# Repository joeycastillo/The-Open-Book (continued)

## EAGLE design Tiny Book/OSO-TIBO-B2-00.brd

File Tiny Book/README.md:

# The Tiny Book

Okay I'm going to be completely honest: I have wandered pretty far from the original prompt with this one. The theory was let's make a less expensive, smaller version of the Open Book with as much of its functionality as possible. With variant B, tiny book has instead become a this very quixotic experiment in form and intent, as well as a playground for new tech like [Good Display's touch screen 2.7" EPD](https://zh-tw.buyepaper.com/products/e-ink-touchscreen-27inch-spi-interface-china-e-ink-manufacturer). 

Variant A (with the cap touch slider) is still here but the touch screen kind of renders it moot. Variant B might be a dead end too, but I think it'll have been worth building for the lessons learned along the way. You could also probably redesign it around an ESP32 or NRF52840 and wind up with something more useful, but there are enough new things in this that I figured I'd stick with the SAMD51 for now since I know the chip so well.

- Features that are basically the same as the Open Book:
    - Battery charging
    - Indicator LEDs
    - 4MB QSPI Flash (up from 2MB)
    - MicroSD slot
    - Enable switch
    - Lock button
    - Reset button
    - Serial port
    - VBAT and VBUS monitors
    - Neopixel

- Features that are similar, and the differences:
    - E-Paper screen. Still has partial refresh, but it's smaller (2.7" instead of 4.2").
    - Instead of seven buttons on the front, the E-Paper display has a capacitive touch matrix that detects touches and gestures (and has an interrupt pin).
    - Microcontroller: it's still a SAMD51 with native USB and the same amount of Flash and RAM, but in a QFN48 package, so fewer pins (and sadly less hand-solderability).
    - The I2C port is now JST-SH (STEMMA-QT) due to size constraints.

- Things that are gone, and strategies for doing without:
    - One STEMMA port instead of two, but it's a really versatile pin. It's a DAC pin so you can speaker with it, or configure it as analog input for a mic or potentiometer, PWM it for an LED, run a Neopixel strip or use it as GPIO for a button.
    - Babel chip. The CircuitPython Babel library supports just putting babel.bin on the QSPI flash chip (and since it's twice the size, you'll still have the same amount of space left over for code).
    - Feather compatibility. Sorry. It would be rad to be able to support FeatherWings but there's just not enough room (or pins).

In the course of this experiment, I ran across a very old design concept that imagined a hinged device with a second e-paper screen on a separate board. So I threw one together, using a [9-pin connector](https://www.adafruit.com/product/4350) (like Adafruit uses on the [MONSTER M4SK](https://www.adafruit.com/product/4343)) to bring over SPI, I2C and one extra signal. A SAMD09 on the secondary board (running Adafruit's Seesaw firmware) gives us more pins for more toys.

- Features that got moved to the secondary board or nerfed.
    - Headphone jack (mono instead of stereo) now lives on the secondary board. I sense that the audio quality may not be as good, since the signal has to travel over a 9-pin connector right next to the I2C signals, but we'll find out.
    - Inline mic input moves over with the headphone jack, but alas there is no longer any provision for recording sound (I removed the mic preamp since there's no spare wire to send a mic signal back to the main board). You can still bias the mic input pin and detect up to three types of button presses from the inline button.

- New features on the secondary board
    - A second 2.7" e-paper display. Pads are there for a touch screen and it's in theory connected to pins on the SAMD09 that *could* support I2C. But this would require some kind of passthrough of I2C messages that I'd have to implement in the SAMD09 firmware. My plan is to use a cheaper non-touchscreen display and only have the main screen be a touch screen.
    - An extra status LED. I'm thinking blue?
    - Speaking of LED's: a PWM-enabled bank of five white LED's along the right (left?) side of the board. I call it a reading light, but they'll shine right at your face if you turn them on. There might be some way to fold the device that coaxes them into illuminating the main screen.
    - Speaking of folding the device: a voltage divider labeled "Hinge?" that I might be able to turn into some kind of hinge position detector using a flex PCB. I honestly have no idea.
    - A real-time clock, because I had room (and because I think this could actually make for a sweet clock).
    - A buzzer for making noises (because it might as well be a sweet alarm clock).
    - A light sensor (because I had a pin leftover).

oh also because i haven't written down the board nomenclature anywhere, this is what i mean by OSO-TIBO-B1-00:

- OSO = Oddly Specific Objects
- TIBO = TIny BOok, the project name
- B = Variant, A-Z, some major version of the board with a specific piece of tech or form factor that makes it unique.
- 1 = Subassembly, 1-9. I doubt I'll ever come up with a project that involves more than 9 PCBs.
- 00 = revision, 00-99. Usually starts at 01, but if I'm really unsure of something I'll start at 00.

I'll update this once the boards come in and I actually assemble one of these.

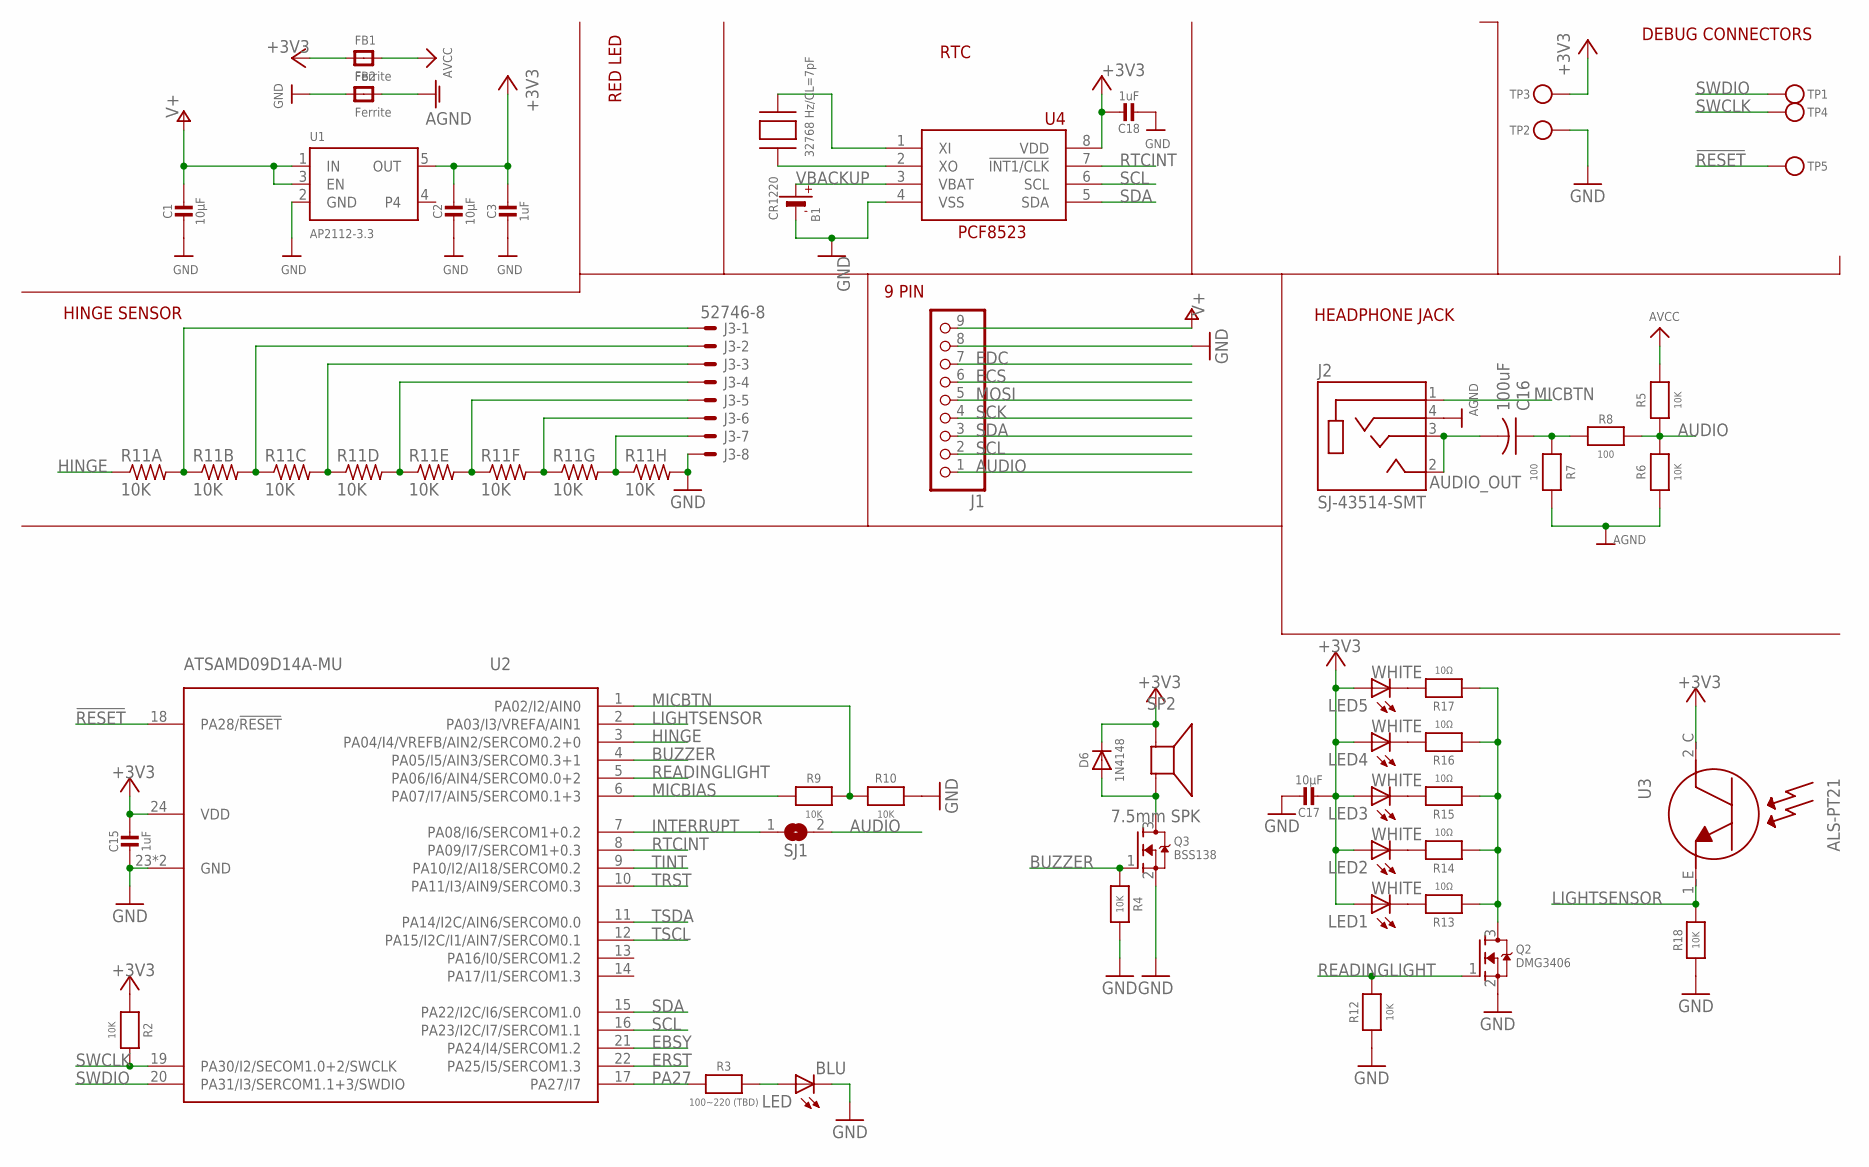
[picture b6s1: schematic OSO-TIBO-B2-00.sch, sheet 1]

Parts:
B1: CR1220
C1, C2, C17: 10µF; 0805-NO
C3, C15, C18: 1uF; 0805-NO
C16: 100uF; C1210
D6: 1N4148; SOD-123
FB1, FB2: Ferrite; 0805
J1: HEADER-1X9_JSTSH; JST_SH9
J2: SJ-43514-SMT; CUI_SJ-43514-SMT
J3: 52746-8
LED: BLU; CHIPLED_0805
LED1, LED2, LED3, LED4, LED5: WHITE; CHIPLED_0805
Q2: DMG3406; SOT23-WIDE
Q3: BSS138; SOT23-WIDE
R2, R4, R9, R10, R12, R18: 10K; 0805-NO
R3: 100~220 (TBD); 0805-NO
R5, R6: 10K; _0805MP
R7, R8: 100; _0805MP
R11: 10K; EXB2HV
R13, R14, R15, R16, R17: 10Ω; 0805-NO
SJ1: SOLDERJUMPERREFLOW_NOPASTE; SOLDERJUMPER_REFLOW_NOPASTE
SP2: 7.5mm SPK; BUZZER_SMT_5MM
TP1, TP2, TP3, TP4, TP5: TESTPOINTROUND2MMNO; TESTPOINT_ROUND_2MM_NO
U1: AP2112-3.3; SOT23-5
U2: ATSAMD09D14A-MU; QFN24_4MM
U3: ALS-PT21; ALS-PT26-21C
U4: PCF8523T; SOIC8_150MIL
X1: 32768 Hz/CL=7pF; XTAL3215

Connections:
!RESET: TP5.P$1, U2.18 (PA28/!RESET)
+3V3: C2.1, C3.1, C15.1, C17.2, C18.1, D6.C, FB1.1, LED1.A, LED2.A, LED3.A, LED4.A, LED5.A, R2.1, SP2.-, TP3.P$1, U1.5 (OUT), U2.24 (VDD), U3.2_C (C), U4.8 (VDD); also elsewhere on the board
AGND: FB2.2, J2.4 (RING2), R6.2, R7.1
AUDIO: J1.1, R5.2, R6.1, R8.1, SJ1.2
AUDIO_OUT: C16.2, J2.2 (TIP), J2.3 (RING1)
AVCC: FB1.2, R5.1
BUZZER: Q3.1 (G), R4.1, U2.4 (PA05/I5/AIN3/SERCOM0.3+1)
EBSY: U2.21 (PA24/I4/SERCOM1.2); also elsewhere on the board
ECS: J1.6; also elsewhere on the board
EDC: J1.7; also elsewhere on the board
ERST: U2.22 (PA25/I5/SERCOM1.3); also elsewhere on the board
GND: B1.-, C1.2, C2.2, C3.2, C15.2, C17.1, C18.2, FB2.1, J1.8, J3.8, LED.C, Q2.2 (S), Q3.2 (S), R4.2, R10.2, R11.9 (2), R12.1, R18.1, TP2.P$1, U1.2 (GND), U2.23 (GND), U2.THERM (GND), U4.4 (VSS); also elsewhere on the board
HINGE: R11.1, U2.3 (PA04/I4/VREFB/AIN2/SERCOM0.2+0)
INTERRUPT: SJ1.1, U2.7 (PA08/I6/SERCOM1+0.2)
LIGHTSENSOR: R18.2, U2.2 (PA03/I3/VREFA/AIN1), U3.1_E (E)
MICBIAS: R9.1, U2.6 (PA07/I7/AIN5/SERCOM0.1+3)
MICBTN: J2.1 (SLEEVE), R9.2, R10.1, U2.1 (PA02/I2/AIN0)
MOSI: J1.5; also elsewhere on the board
unnamed: C16.1, R7.2, R8.2
unnamed: LED1.C, R13.2
unnamed: J3.1, R11.2 (1), R11.16 (2)
unnamed: J3.2, R11.3 (1), R11.15 (2)
unnamed: LED.A, R3.2
unnamed: J3.3, R11.4 (1), R11.14 (2)
unnamed: J3.4, R11.5 (1), R11.13 (2)
unnamed: J3.5, R11.6 (1), R11.12 (2)
unnamed: J3.6, R11.7 (1), R11.11 (2)
unnamed: J3.7, R11.8 (1), R11.10 (2)
unnamed: D6.A, Q3.3 (D), SP2.+
unnamed: LED2.C, R14.2
unnamed: LED3.C, R15.2
unnamed: LED4.C, R16.2
unnamed: LED5.C, R17.2
PA27: R3.1, U2.17 (PA27/I7)
READINGLIGHT: Q2.1 (G), R12.2, U2.5 (PA06/I6/AIN4/SERCOM0.0+2)
READINGLIGHT_SINK: Q2.3 (D), R13.1, R14.1, R15.1, R16.1, R17.1
RTCINT: U2.8 (PA09/I7/SERCOM1+0.3), U4.7 (!INT1/CLK)
SCK: J1.4; also elsewhere on the board
SCL: J1.2, U2.16 (PA23/I2C/I7/SERCOM1.1), U4.6 (SCL)
SDA: J1.3, U2.15 (PA22/I2C/I6/SERCOM1.0), U4.5 (SDA)
SWCLK: R2.2, TP4.P$1, U2.19 (PA30/I2/SECOM1.0+2/SWCLK)
SWDIO: TP1.P$1, U2.20 (PA31/I3/SERCOM1.1+3/SWDIO)
TINT: U2.9 (PA10/I2/AI18/SERCOM0.2); also elsewhere on the board
TRST: U2.10 (PA11/I3/AIN9/SERCOM0.3); also elsewhere on the board
TSCL: U2.12 (PA15/I2C/I1/AIN7/SERCOM0.1); also elsewhere on the board
TSDA: U2.11 (PA14/I2C/AIN6/SERCOM0.0); also elsewhere on the board
V+: C1.1, J1.9, U1.1 (IN), U1.3 (EN)
VBACKUP: B1.+$1 (+), B1.+$2 (+), U4.3 (VBAT)
XIN_RTC: U4.1 (XI), X1.P$2
XOUT_RTC: U4.2 (XO), X1.P$1

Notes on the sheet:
DEBUG CONNECTORS
HINGE SENSOR
RED LED
9 PIN
HEADPHONE JACK
RTC

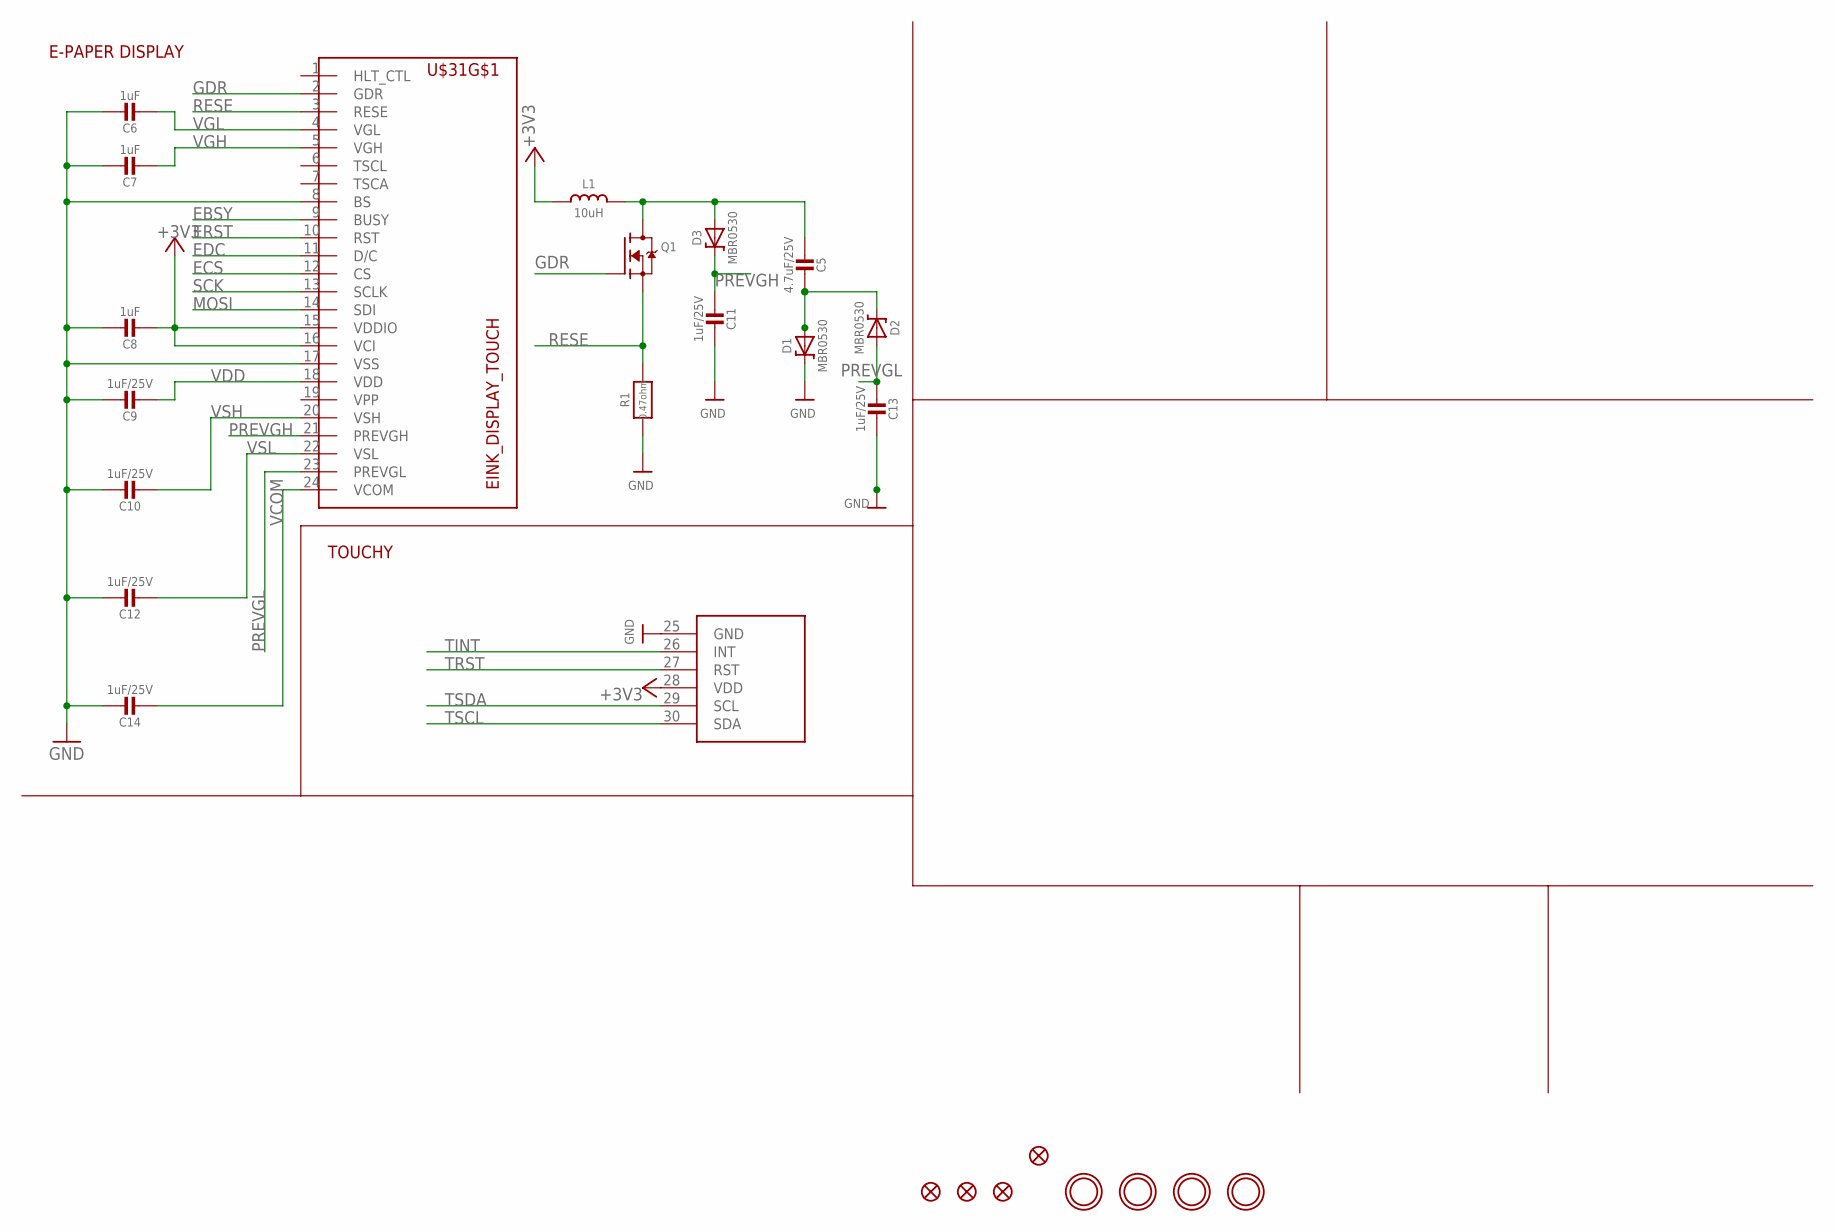
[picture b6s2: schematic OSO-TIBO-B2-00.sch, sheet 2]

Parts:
C5: 4.7uF/25V; 0805-NO
C6, C7, C8: 1uF; 0805_10MGAP
C9, C10, C11, C12, C13, C14: 1uF/25V; 0805_10MGAP
D1, D2, D3: MBR0530; SOD-123
FID1, FID2, FID3, FID4: FIDUCIAL_1MM
L1: 10uH; MICROBUILDER_INDUCTOR_4X4MM_NR401_BIGPADS
Q1: IRLML0100; SOT23-3
R1: 0.47ohm; 0805_10MGAP
U$1, U$4, U$5, U$7: MOUNTINGHOLE2.5; MOUNTINGHOLE_2.5_PLATED
U$31: EINK_DISPLAY_TOUCH; EINK_DISPLAY_2_7_IN_TOUCH

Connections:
+3V3: C8.2, L1.P$1 (1), U$31.15 (VDDIO), U$31.16 (VCI), U$31.28 (VDD); also elsewhere on the board
EBSY: U$31.9 (BUSY); also elsewhere on the board
ECS: U$31.12 (CS); also elsewhere on the board
EDC: U$31.11 (D/C); also elsewhere on the board
ERST: U$31.10 (RST); also elsewhere on the board
GDR: Q1.1 (G), U$31.2 (GDR)
GND: C6.1, C7.1, C8.1, C9.1, C10.1, C11.2, C12.1, C13.2, C14.1, D1.C, R1.2, U$31.8 (BS), U$31.17 (VSS), U$31.25 (GND); also elsewhere on the board
MOSI: U$31.14 (SDI); also elsewhere on the board
unnamed: C5.2, D1.A, D2.C
unnamed: C5.1, D3.A, L1.P$2 (2), Q1.3 (D)
PREVGH: C11.1, D3.C, U$31.21 (PREVGH)
PREVGL: C13.1, D2.A, U$31.23 (PREVGL)
RESE: Q1.2 (S), R1.1, U$31.3 (RESE)
SCK: U$31.13 (SCLK); also elsewhere on the board
TINT: U$31.26 (INT); also elsewhere on the board
TRST: U$31.27 (RST); also elsewhere on the board
TSCL: U$31.30 (SDA); also elsewhere on the board
TSDA: U$31.29 (SCL); also elsewhere on the board
VCOM: C14.2, U$31.24 (VCOM)
VDD: C9.2, U$31.18 (VDD)
VGH: C7.2, U$31.5 (VGH)
VGL: C6.2, U$31.4 (VGL)
VSH: C10.2, U$31.20 (VSH)
VSL: C12.2, U$31.22 (VSL)

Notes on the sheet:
E-PAPER DISPLAY
TOUCHY

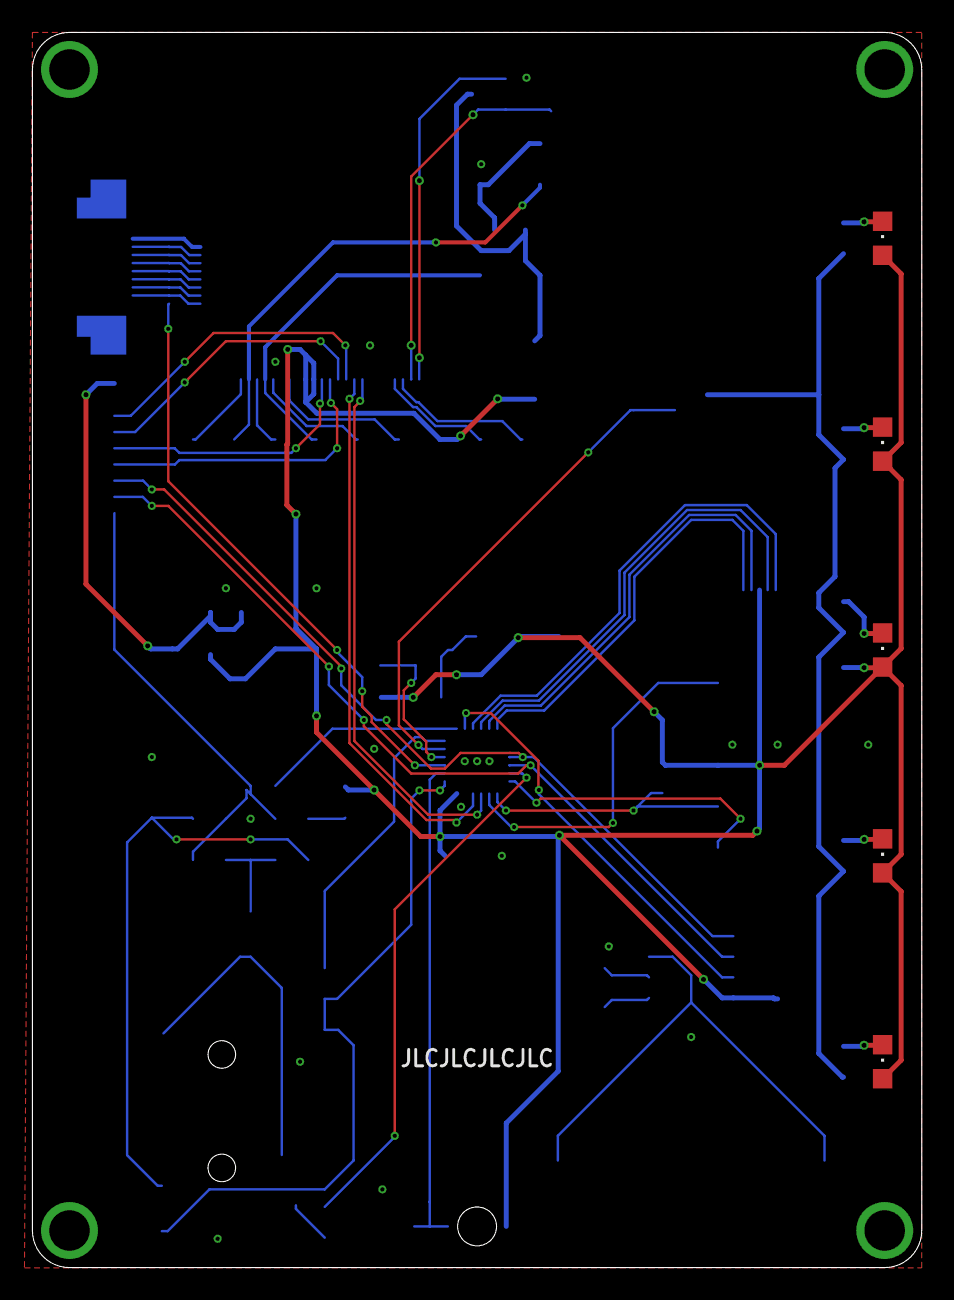
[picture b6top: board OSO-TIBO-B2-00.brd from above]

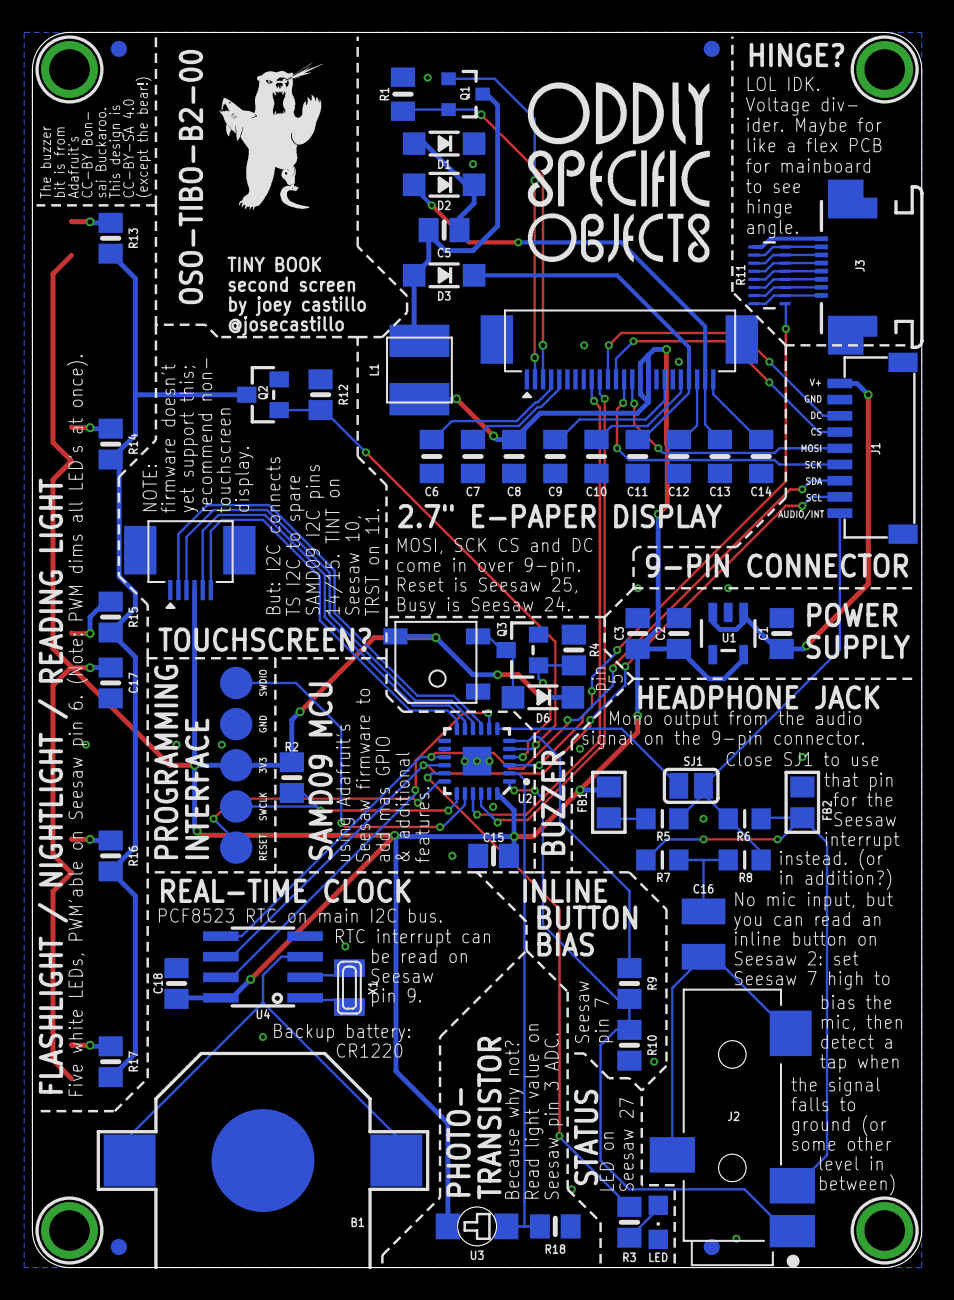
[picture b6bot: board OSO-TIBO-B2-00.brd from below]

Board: 2 copper layers, 54.9 x 76.2 mm, 78 parts (72 on the bottom side), 62 nets.

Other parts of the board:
U$37: OSO_WORDMARK_THREELINE_450MIL_1000DPI
U$44: OSO_BEAR_250X360MIL_1000DPI

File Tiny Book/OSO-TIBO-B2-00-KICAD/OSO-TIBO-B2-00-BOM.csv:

Reference, Quantity, Value, Footprint, Datasheet
B1 ,1,"CR1220","OSO-TIBO-B2-00:CR1220",""
C1 C17 C2 ,3,"10µF","OSO-TIBO-B2-00:0805-NO",""
C10 C11 C12 C13 C14 C9 ,6,"1uF/25V","OSO-TIBO-B2-00:0805_10MGAP",""
C16 ,1,"100uF","OSO-TIBO-B2-00:C1210",""
C15 C18 C3 ,3,"1uF","OSO-TIBO-B2-00:0805-NO",""
C5 ,1,"4.7uF/25V","OSO-TIBO-B2-00:0805-NO",""
C6 C7 C8 ,3,"1uF","OSO-TIBO-B2-00:0805_10MGAP",""
D1 D2 D3 ,3,"MBR0530","OSO-TIBO-B2-00:SOD-123",""
D6 ,1,"1N4148","OSO-TIBO-B2-00:SOD-123",""
FB1 FB2 ,2,"Ferrite","OSO-TIBO-B2-00:0805",""
FID1 FID2 FID3 FID4 ,4,"FIDUCIAL_1MM","OSO-TIBO-B2-00:FIDUCIAL_1MM",""
J1 ,1,"HEADER-1X9_JSTSH","OSO-TIBO-B2-00:JST_SH9",""
J2 ,1,"SJ-43514-SMT","OSO-TIBO-B2-00:CUI_SJ-43514-SMT",""
J3 ,1,"52746-8","OSO-TIBO-B2-00:52746-8",""
L1 ,1,"10uH","OSO-TIBO-B2-00:MICROBUILDER_INDUCTOR_4X4MM_NR401_BIGPADS",""
LED1 LED2 LED3 LED4 LED5 ,5,"WHITE","OSO-TIBO-B2-00:CHIPLED_0805",""
LED6 ,1,"BLU","OSO-TIBO-B2-00:CHIPLED_0805",""
Q1 ,1,"IRLML0100","OSO-TIBO-B2-00:SOT23-3",""
Q2 ,1,"DMG3406","OSO-TIBO-B2-00:SOT23-WIDE",""
Q3 ,1,"BSS138","OSO-TIBO-B2-00:SOT23-WIDE",""
R1 ,1,"0.47ohm","OSO-TIBO-B2-00:0805_10MGAP",""
R11 ,1,"10K","OSO-TIBO-B2-00:EXB2HV",""
R13 R14 R15 R16 R17 ,5,"10Ω","OSO-TIBO-B2-00:0805-NO",""
R10 R12 R18 R2 R4 R9 ,6,"10K","OSO-TIBO-B2-00:0805-NO",""
R3 ,1,"100~~220 (TBD)","OSO-TIBO-B2-00:0805-NO",""
R5 R6 ,2,"10K","OSO-TIBO-B2-00:_0805MP",""
R7 R8 ,2,"100","OSO-TIBO-B2-00:_0805MP",""
SJ1 ,1,"SOLDERJUMPERREFLOW_NOPASTE","OSO-TIBO-B2-00:SOLDERJUMPER_REFLOW_NOPASTE",""
SP2 ,1,"7.5mm SPK","OSO-TIBO-B2-00:BUZZER_SMT_5MM",""
TP1 TP2 TP3 TP4 TP5 ,5,"TESTPOINTROUND2MMNO","OSO-TIBO-B2-00:TESTPOINT_ROUND_2MM_NO",""
U$1 U$4 U$5 U$7 ,4,"MOUNTINGHOLE2.5","OSO-TIBO-B2-00:MOUNTINGHOLE_2.5_PLATED",""
U$31 ,1,"EINK_DISPLAY_TOUCH","OSO-TIBO-B2-00:EINK_DISPLAY_2_7_IN_TOUCH",""
U1 ,1,"AP2112-3.3","OSO-TIBO-B2-00:SOT23-5",""
U2 ,1,"ATSAMD09D14A-MU","OSO-TIBO-B2-00:QFN24_4MM",""
U3 ,1,"ALS-PT21","OSO-TIBO-B2-00:ALS-PT26-21C",""
U4 ,1,"PCF8523T","OSO-TIBO-B2-00:SOIC8_150MIL",""
X1 ,1,"32768 Hz/CL=7pF","OSO-TIBO-B2-00:XTAL3215",""

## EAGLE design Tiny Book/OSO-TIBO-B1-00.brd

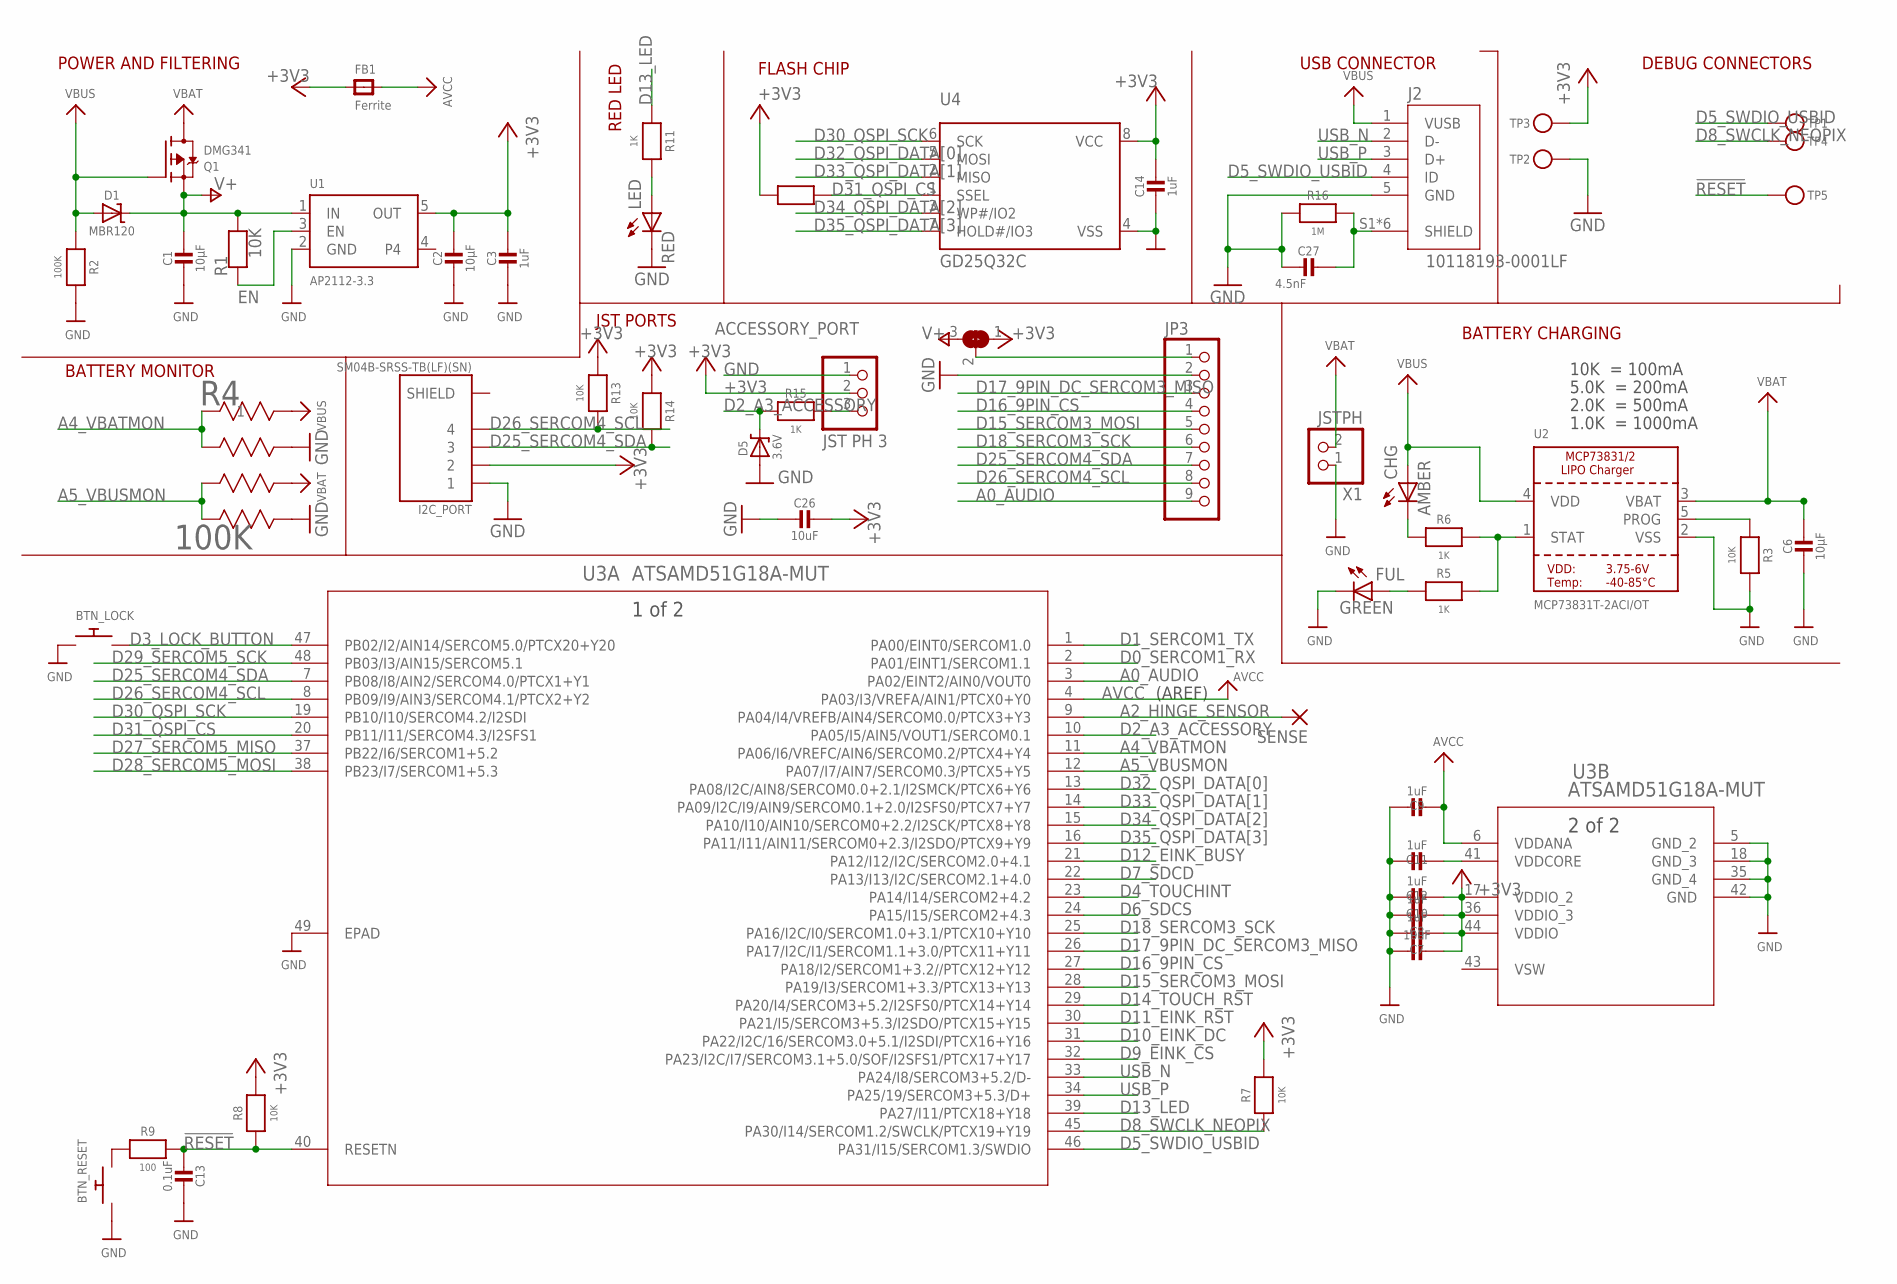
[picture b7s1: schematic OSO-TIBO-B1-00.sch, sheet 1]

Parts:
ACCESSORY_PORT: JST PH 3; JSTPH3
BTN_LOCK: SWITCH_PUSHBUTTONC&K_KSS; BTN_CK_KSS
BTN_RESET: SWITCH_PUSHBUTTONC&K_KSS; BTN_CK_KSS
C1, C2, C6: 10µF; 0805-NO
C3, C8, C9: 1uF; 0805-NO
C7, C26: 10uF; 0805-NO
C10, C11, C12, C14: 1uF; 0805_10MGAP
C13: 0.1uF; 0805_10MGAP
C27: 4.5nF; 0805-NO
CHG: AMBER; CHIPLED_0805
D1: MBR120; SOD-123
D5: 3.6V; SOD-123
FB1: Ferrite; 0805
FUL: GREEN; CHIPLED_0805
I2C_PORT: SM04B-SRSS-TB(LF)(SN); JST_SM04B-SRSS-TB(LF)(SN)
J2: 10118193-0001LF; FCI_10118193-0001LF
JP3: HEADER-1X9_JSTSH; JST_SH9
LED: RED; CHIPLED_0805
Q1: DMG341; SOT23-R
R1, R3, R7, R8, R10, R13, R14: 10K; 0805-NO
R2: 100K; 0805-NO
R4: 100K; EXBV8V
R5, R6, R11: 1K; 0805-NO
R9: 100; 0805_10MGAP
R15: 1K; _0805MP
R16: 1M; 0805-NO
SENSE: SMD5; SMD2,54-5,08
SJ1: SOLDERJUMPER_2WAY; SOLDERJUMPER_2WAY_OPEN_NOPASTE
TP1, TP2, TP3, TP4, TP5: TESTPOINTROUND2MMNO; TESTPOINT_ROUND_2MM_NO
U1: AP2112-3.3; SOT23-5
U2: MCP73831T-2ACI/OT; SOT23-5
U3: ATSAMD51G18A-MUT; QFN48_7X7MC
U4: GD25Q32C; MICROBUILDER_SOIC8_150MIL
X1: JSTPH; JSTPH2

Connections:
!RESET: C13.2, R8.1, R9.2, TP5.P$1, U3.40 (RESETN)
+3V3: ACCESSORY_PORT.2, C2.1, C3.1, C7.2, C8.2, C10.2, C12.2, C14.1, C26.1, FB1.1, I2C_PORT.2, R7.2, R8.2, R10.2, R13.1, R14.1, SJ1.1, TP3.P$1, U1.5 (OUT), U3.17 (VDDIO_2), U3.36 (VDDIO_3), U3.44 (VDDIO), U4.8 (VCC); also elsewhere on the board
A0_AUDIO: JP3.9, U3.3 (PA02/EINT2/AIN0/VOUT0)
A2_HINGE_SENSOR: SENSE.1, U3.9 (PA04/I4/VREFB/AIN4/SERCOM0.0/PTCX3+Y3)
A4_VBATMON: R4.1, R4.2, U3.11 (PA06/I6/VREFC/AIN6/SERCOM0.2/PTCX4+Y4)
A5_VBUSMON: R4.3, R4.4, U3.12 (PA07/I7/AIN7/SERCOM0.3/PTCX5+Y5)
AVCC: C9.2, FB1.2, U3.4 (PA03/I3/VREFA/AIN1/PTCX0+Y0), U3.6 (VDDANA)
D0_SERCOM1_RX: U3.2 (PA01/EINT1/SERCOM1.1); also elsewhere on the board
D1_SERCOM1_TX: U3.1 (PA00/EINT0/SERCOM1.0); also elsewhere on the board
D2_A3_ACCESSORY: D5.C, R15.2, U3.10 (PA05/I5/AIN5/VOUT1/SERCOM0.1)
D3_LOCK_BUTTON: BTN_LOCK.P$2, U3.47 (PB02/I2/AIN14/SERCOM5.0/PTCX20+Y20)
D4_TOUCHINT: U3.23 (PA14/I14/SERCOM2+4.2); also elsewhere on the board
D5_SWDIO_USBID: J2.4 (ID), TP1.P$1, U3.46 (PA31/I15/SERCOM1.3/SWDIO)
D6_SDCS: U3.24 (PA15/I15/SERCOM2+4.3); also elsewhere on the board
D7_SDCD: U3.22 (PA13/I13/I2C/SERCOM2.1+4.0); also elsewhere on the board
D8_SWCLK_NEOPIX: R7.1, TP4.P$1, U3.45 (PA30/I14/SERCOM1.2/SWCLK/PTCX19+Y19); also elsewhere on the board
D9_EINK_CS: U3.32 (PA23/I2C/I7/SERCOM3.1+5.0/SOF/I2SFS1/PT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); also elsewhere on the board
D10_EINK_DC: U3.31 (PA22/I2C/16/SERCOM3.0+5.1/I2SDI/PTCX16+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); also elsewhere on the board
D11_EINK_RST: U3.30 (PA21/I5/SERCOM3+5.3/I2SDO/PTCX15+Y15); also elsewhere on the board
D12_EINK_BUSY: U3.21 (PA12/I12/I2C/SERCOM2.0+4.1); also elsewhere on the board
D13_LED: R11.1, U3.39 (PA27/I11/PTCX18+Y18)
D14_TOUCH_RST: U3.29 (PA20/I4/SERCOM3+5.2/I2SFS0/PTCX14+Y14); also elsewhere on the board
D15_SERCOM3_MOSI: JP3.5, U3.28 (PA19/I3/SERCOM1+3.3/PTCX13+Y13); also elsewhere on the board
D16_9PIN_CS: JP3.4, U3.27 (PA18/I2/SERCOM1+3.2//PTCX12+Y12)
D17_9PIN_DC_SERCOM3_MISO: JP3.3, U3.26 (PA17/I2C/I1/SERCOM1.1+3.0/PTCX11+Y11)
D18_SERCOM3_SCK: JP3.6, U3.25 (PA16/I2C/I0/SERCOM1.0+3.1/PTCX10+Y10); also elsewhere on the board
D25_SERCOM4_SDA: I2C_PORT.3, JP3.7, R14.2, U3.7 (PB08/I8/AIN2/SERCOM4.0/PTCX1+Y1); also elsewhere on the board
D26_SERCOM4_SCL: I2C_PORT.4, JP3.8, R13.2, U3.8 (PB09/I9/AIN3/SERCOM4.1/PTCX2+Y2); also elsewhere on the board
D27_SERCOM5_MISO: U3.37 (PB22/I6/SERCOM1+5.2); also elsewhere on the board
D28_SERCOM5_MOSI: U3.38 (PB23/I7/SERCOM1+5.3); also elsewhere on the board
D29_SERCOM5_SCK: U3.48 (PB03/I3/AIN15/SERCOM5.1); also elsewhere on the board
D30_QSPI_SCK: U3.19 (PB10/I10/SERCOM4.2/I2SDI), U4.6 (SCK)
D31_QSPI_CS: R10.1, U3.20 (PB11/I11/SERCOM4.3/I2SFS1), U4.1 (SSEL)
D32_QSPI_DATA[0]: U3.13 (PA08/I2C/AIN8/SERCOM0.0+2.1/I2SMCK/PTCX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), U4.5 (MOSI)
D33_QSPI_DATA[1]: U3.14 (PA09/I2C/I9/AIN9/SERCOM0.1+2.0/I2SFS0/P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), U4.2 (MISO)
D34_QSPI_DATA[2]: U3.15 (PA10/I10/AIN10/SERCOM0+2.2/I2SCK/PTCX8+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), U4.3 (WP#/IO2)
D35_QSPI_DATA[3]: U3.16 (PA11/I11/AIN11/SERCOM0+2.3/I2SDO/PTCX9+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), U4.7 (HOLD#/IO3)
EN: R1.1, U1.3 (EN); also elsewhere on the board
GND: ACCESSORY_PORT.1, BTN_LOCK.P$1, BTN_RESET.P$1, C1.2, C2.2, C3.2, C6.2, C7.1, C8.1, C9.1, C10.1, C11.1, C12.1, C13.1, C14.2, C26.2, C27.2, D5.A, FUL.C, I2C_PORT.1, J2.5 (GND), JP3.2, LED.C, R2.2, R3.2, R4.5, R4.7, R16.2, TP2.P$1, U1.2 (GND), U2.2 (VSS), U3.5 (GND_2), U3.18 (GND_3), U3.35 (GND_4), U3.42 (GND), U3.49 (EPAD), U4.4 (VSS), X1.1; also elsewhere on the board
unnamed: BTN_RESET.P$2, R9.1
unnamed: CHG.C, R6.1
unnamed: JP3.1, SJ1.2
unnamed: LED.A, R11.2
unnamed: FUL.A, R5.1
PROG: R3.1, U2.5 (PROG)
SHIELD: C27.1, J2.S1 (SHIELD), J2.S2 (SHIELD), J2.S3 (SHIELD), J2.S4 (SHIELD), J2.S5 (SHIELD), J2.S6 (SHIELD), R16.1
STAT: R5.2, R6.2, U2.1 (STAT)
USB_N: J2.2 (D-), U3.33 (PA24/I8/SERCOM3+5.2/D-)
USB_P: J2.3 (D+), U3.34 (PA25/19/SERCOM3+5.3/D+)
V+: C1.1, D1.C, Q1.2 (S), R1.2, SJ1.3, U1.1 (IN)
VBAT: C6.1, Q1.3 (D), R4.6, U2.3 (VBAT), X1.2
VBUS: CHG.A, D1.A, J2.1 (VUSB), Q1.1 (G), R2.1, R4.8, U2.4 (VDD)
VDDCORE: C11.2, U3.41 (VDDCORE)
VSW: U3.43 (VSW)
_ACCESSORY: ACCESSORY_PORT.3, R15.1

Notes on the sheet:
POWER AND FILTERING
10K = 100mA
5.0K = 200mA
2.0K = 500mA
1.0K = 1000mA
BATTERY CHARGING
DEBUG CONNECTORS
USB CONNECTOR
BATTERY MONITOR
FLASH CHIP
RED LED
JST PORTS
(AREF)

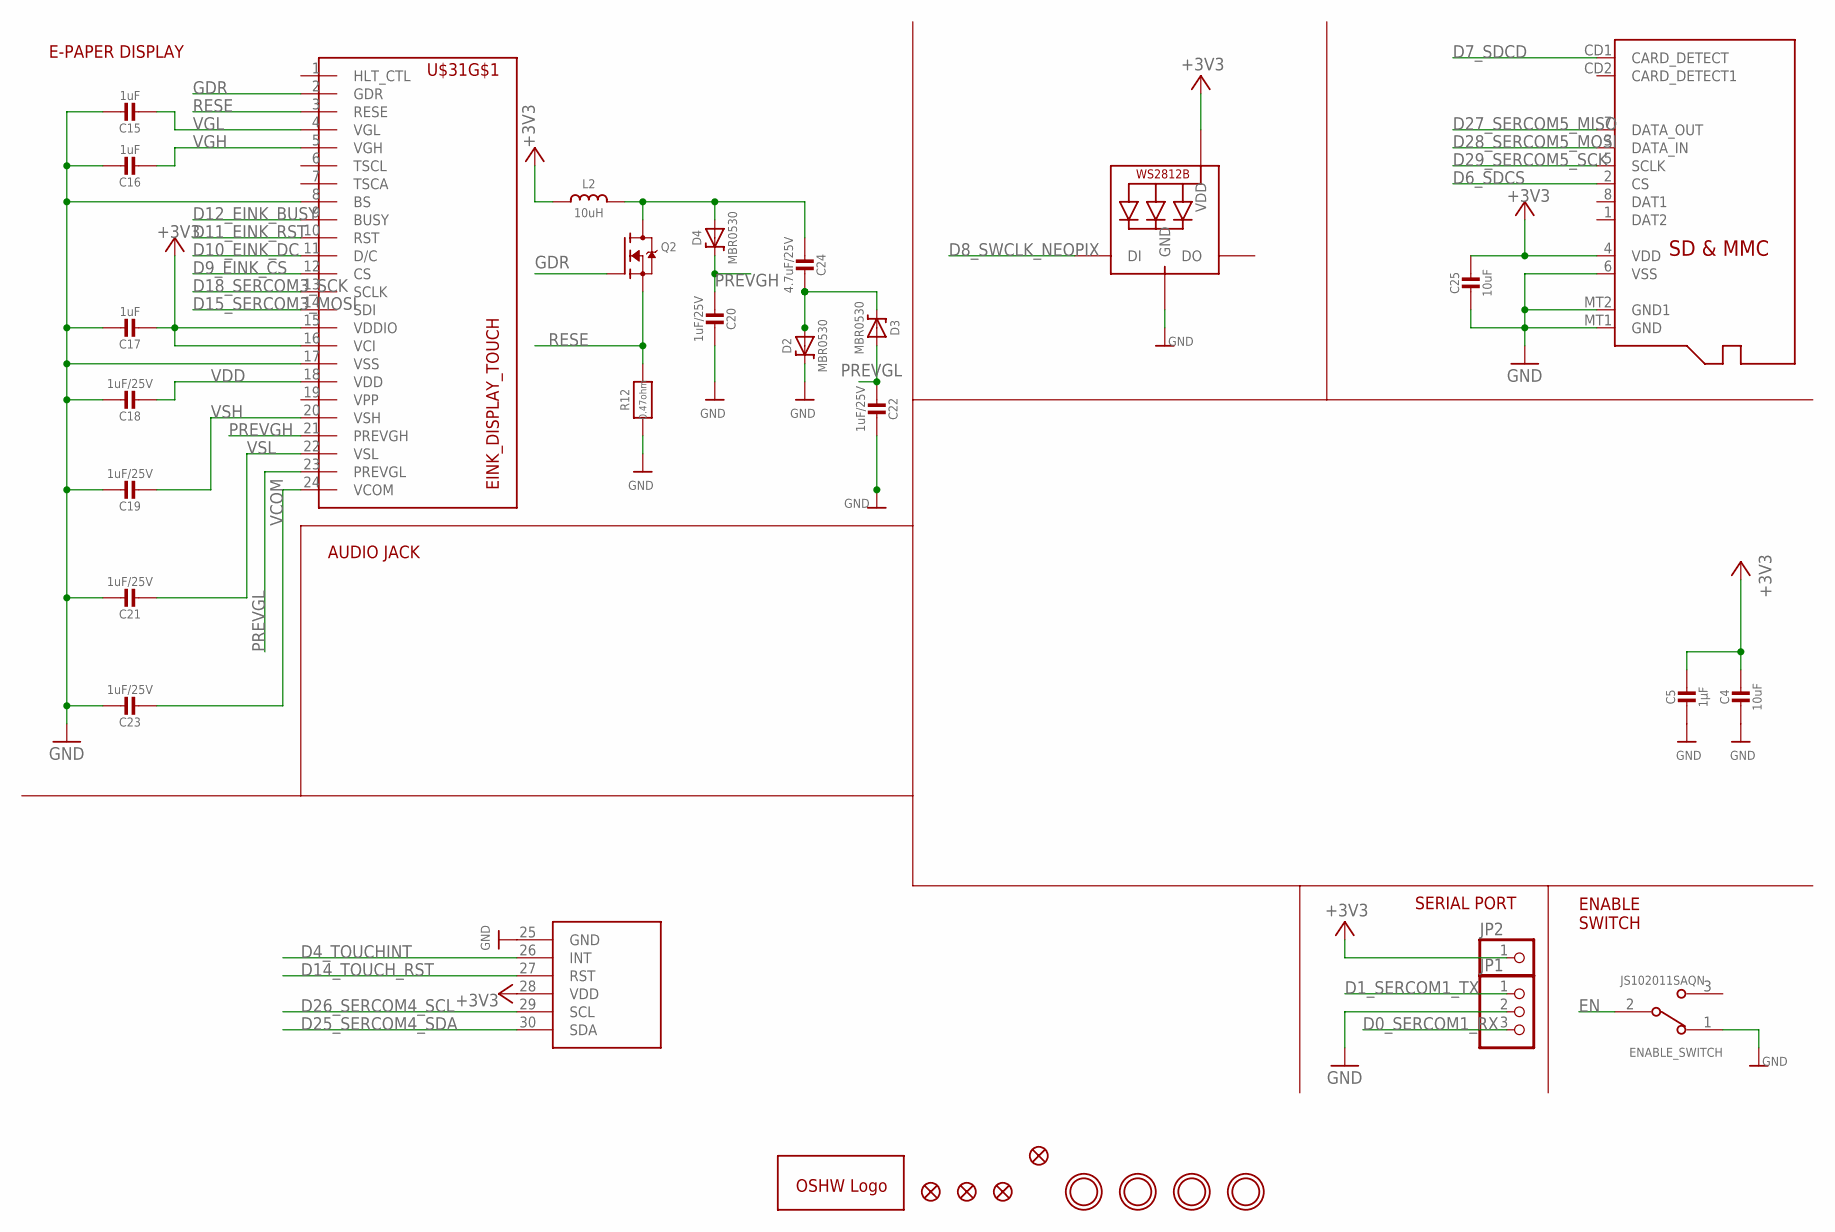
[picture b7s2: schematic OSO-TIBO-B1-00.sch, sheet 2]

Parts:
C4: 10uF; 0805-NO
C5: 1µF; 0805-NO
C15, C16, C17: 1uF; 0805_10MGAP
C18, C19, C20, C21, C22, C23: 1uF/25V; 0805_10MGAP
C24: 4.7uF/25V; 0805-NO
C25: 10uF; 0805_10MGAP
D2, D3, D4: MBR0530; SOD-123
ENABLE_SWITCH: JS102011SAQN; SW_JS102011SAQN
FID1, FID2, FID3, FID4: FIDUCIAL_1MM
GOLD_ORB_SM1: OSHWLOGOLOGO5MM; OSHW_5MM
JP1: PINHD-1X3; 1X03
JP2: PINHD-1X1; 1X01
L2: 10uH; MICROBUILDER_INDUCTOR_4X4MM_NR401_BIGPADS
MICROSD: MICROSD
NEOPIXEL: WS2812B_4020
Q2: IRLML0100; SOT23-3
R12: 0.47ohm; 0805_10MGAP
U$1, U$4, U$5, U$7: MOUNTINGHOLE2.5; MOUNTINGHOLE_2.5_PLATED
U$31: EINK_DISPLAY_TOUCH; EINK_DISPLAY_2_7_IN_TOUCH

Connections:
+3V3: C4.1, C5.1, C17.2, C25.1, JP2.1, L2.P$1 (1), MICROSD.4 (VDD), NEOPIXEL.2 (VDD), U$31.15 (VDDIO), U$31.16 (VCI), U$31.28 (VDD); also elsewhere on the board
D0_SERCOM1_RX: JP1.3; also elsewhere on the board
D1_SERCOM1_TX: JP1.1; also elsewhere on the board
D4_TOUCHINT: U$31.26 (INT); also elsewhere on the board
D6_SDCS: MICROSD.2 (CS); also elsewhere on the board
D7_SDCD: MICROSD.CD1 (CARD_DETECT); also elsewhere on the board
D8_SWCLK_NEOPIX: NEOPIXEL.1 (DI); also elsewhere on the board
D9_EINK_CS: U$31.12 (CS); also elsewhere on the board
D10_EINK_DC: U$31.11 (D/C); also elsewhere on the board
D11_EINK_RST: U$31.10 (RST); also elsewhere on the board
D12_EINK_BUSY: U$31.9 (BUSY); also elsewhere on the board
D14_TOUCH_RST: U$31.27 (RST); also elsewhere on the board
D15_SERCOM3_MOSI: U$31.14 (SDI); also elsewhere on the board
D18_SERCOM3_SCK: U$31.13 (SCLK); also elsewhere on the board
D25_SERCOM4_SDA: U$31.30 (SDA); also elsewhere on the board
D26_SERCOM4_SCL: U$31.29 (SCL); also elsewhere on the board
D27_SERCOM5_MISO: MICROSD.7 (DATA_OUT); also elsewhere on the board
D28_SERCOM5_MOSI: MICROSD.3 (DATA_IN); also elsewhere on the board
D29_SERCOM5_SCK: MICROSD.5 (SCLK); also elsewhere on the board
EN: ENABLE_SWITCH.2; also elsewhere on the board
GDR: Q2.1 (G), U$31.2 (GDR)
GND: C4.2, C5.2, C15.1, C16.1, C17.1, C18.1, C19.1, C20.2, C21.1, C22.2, C23.1, C25.2, D2.C, ENABLE_SWITCH.1, JP1.2, MICROSD.6 (VSS), MICROSD.MT1 (GND), MICROSD.MT2 (GND1), NEOPIXEL.4 (GND), R12.2, U$31.8 (BS), U$31.17 (VSS), U$31.25 (GND); also elsewhere on the board
unnamed: C24.2, D2.A, D3.C
unnamed: C24.1, D4.A, L2.P$2 (2), Q2.3 (D)
PREVGH: C20.1, D4.C, U$31.21 (PREVGH)
PREVGL: C22.1, D3.A, U$31.23 (PREVGL)
RESE: Q2.2 (S), R12.1, U$31.3 (RESE)
VCOM: C23.2, U$31.24 (VCOM)
VDD: C18.2, U$31.18 (VDD)
VGH: C16.2, U$31.5 (VGH)
VGL: C15.2, U$31.4 (VGL)
VSH: C19.2, U$31.20 (VSH)
VSL: C21.2, U$31.22 (VSL)

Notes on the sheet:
E-PAPER DISPLAY
ENABLE SWITCH
SERIAL PORT
AUDIO JACK
